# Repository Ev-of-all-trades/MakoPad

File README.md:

# MakoPad
This is a 6 key macropad that I designed in KiCad and is programmed with QMK. It features a 1.8" LCD display, 6 hot-swappable keys, a rotary encoder, and 2 buttons to switch the layers. This Project has been made specially for programmers on FRC 5199 Robot Dolphins From Outer Space to help them with FRC Programming. 

PCB and Schematic
-----------------------------------------------------

Below is A picture of the assembly I made in Fusion 360.
------------------------------------------------------------------------------------
PCB Assembly [mind the crappy displau model, i couldn't find a better one since there wasn't any for the specific one i wanted to use]

Here is the plan for developing the programming
--------------------------------------------------
Phase 1: Keyboard matrix
- Program the keyboard matrix and build the layers
- Test matrix to make sure it works

Phase 2: Rotary encoder
- Add the rotary encoder and rotary encoder switch into the programming
- Program the special functions for the rotary encoder
  - Make it so that whenever the rotary encoder is pressed down, you can rotate the knob to select what function you want to rotary encoder to do
- Test rotation and clicking

Phase 3: Layer buttons
- Program the button to change the keyboard matrix layers
  - The top button switches to the next layer and the bottom one switches to the previous layer

Phase 4: The display
- Make the display interface with the microcontroller

Phase 5: Make it awesome
- Layer-dependent key labels
- Encoder modes
- Custom macros
- Startup screen
- MakoPad logo
- Current layer display
- Key function display

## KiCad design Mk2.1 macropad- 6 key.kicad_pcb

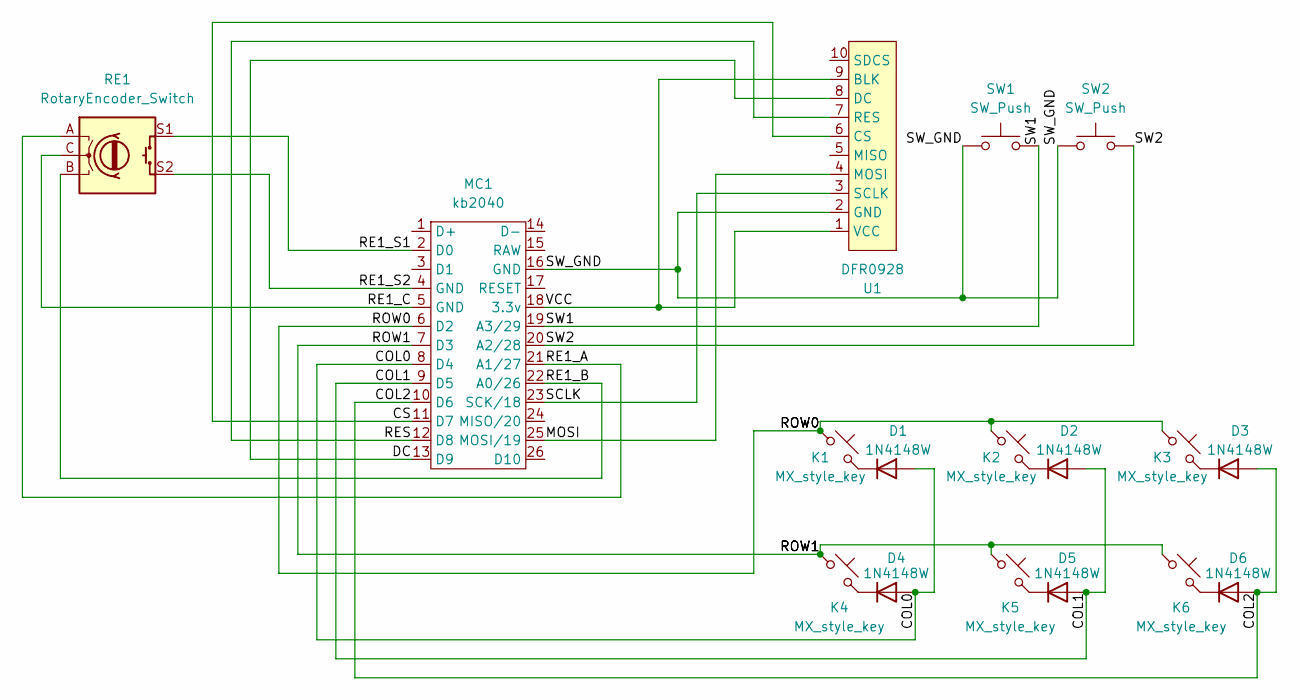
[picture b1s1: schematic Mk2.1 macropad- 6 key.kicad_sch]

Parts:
D1, D2, D3, D4, D5, D6: 1N4148W; D_SOD-123
K1, K2, K3, K4, K5, K6: MX_style_key; Kailh MX hot-swap socket [part #PG151101S11]
MC1: kb2040
RE1: RotaryEncoder_Switch; RotaryEncoder_Alps_EC11E-Switch_Vertical_H20mm
SW1, SW2: SW_Push; SW_PUSH-12mm
U1: DFR0928; Fermion 1.8in 128x160 IPS TFT LCD Display

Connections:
/COL0: D1.2 (A), D4.2 (A), MC1.8 (D4)
/COL1: D2.2 (A), D5.2 (A), MC1.9 (D5)
/COL2: D3.2 (A), D6.2 (A), MC1.10 (D6)
/CS: MC1.11 (D7), U1.6 (CS)
/DC: MC1.13 (D9), U1.8 (DC)
/MOSI: MC1.25 (MOSI/19), U1.4 (MOSI)
/RE1_A: MC1.21 (A1/27), RE1.A
/RE1_B: MC1.22 (A0/26), RE1.B
/RE1_C: MC1.5 (GND), RE1.C
/RE1_S1: MC1.2 (D0), RE1.S1
/RE1_S2: MC1.4 (GND), RE1.S2
/RES: MC1.12 (D8), U1.7 (RES)
/ROW0: K1.1, K2.1, K3.1, MC1.6 (D2)
/ROW1: K4.1, K5.1, K6.1, MC1.7 (D3)
/SCLK: MC1.23 (SCK/18), U1.3 (SCLK)
/SW1: MC1.19 (A3/29), SW1.2
/SW2: MC1.20 (A2/28), SW2.2
/SW_GND: MC1.16 (GND), SW1.1, SW2.1, U1.2 (GND)
/VCC: MC1.18 (3.3v), U1.1 (VCC), U1.9 (BLK)
unnamed: D1.1 (K), K1.2
unnamed: D2.1 (K), K2.2
unnamed: D3.1 (K), K3.2
unnamed: D4.1 (K), K4.2
unnamed: D5.1 (K), K5.2
unnamed: D6.1 (K), K6.2

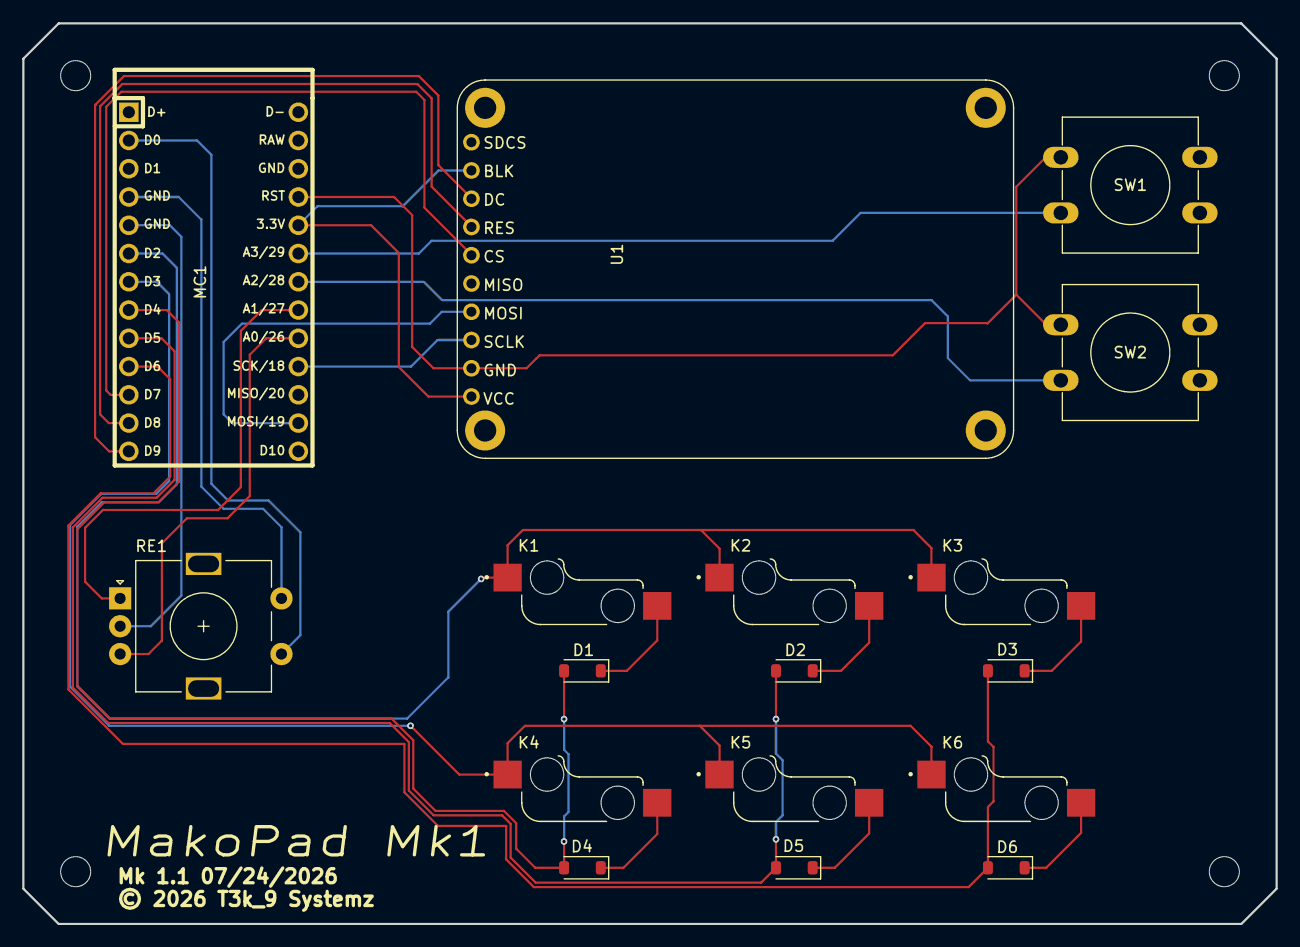
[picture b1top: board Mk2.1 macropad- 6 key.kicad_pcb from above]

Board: 2 copper layers, 112.7 x 80.9 mm, 17 parts (0 on the bottom side), 25 nets.

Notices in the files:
Mk2.1 macropad- 6 key.kicad_pcb:
© 2026 T3k_9 Systemz
